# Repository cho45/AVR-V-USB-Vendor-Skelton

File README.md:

AVR V-USB custom class skelton project
======================================

AVR + V-USB でカスタムUSBデバイスを作るスケルトン
V-USB がスタンダードなリクエストには答えてくれるのでかなり簡潔に書ける。

このデバイスに接続するためのホスト実装のサンプル

 * [./sketch.rb]( ./sketch.rb ) libusb + ruby
 * [./sketch-chrome-app/]( ./sketch-chrome-app/ ) Chrome App

回路図の例 (Eagle)

 * [./circuit/]( ./circuit/ )

## 背景

Mac の場合 HID デバイスへの低レベルアクセスを OS が握っているため、
HID クラスとしてデバイスを作成すると、かえって面倒なことになる ( control_transfer は可能だが、claim_interface が不可能なので他のことは何もできない)。

## 覚書

 * USB_CFG_DEVICE_CLASS を 0xff (vendor)
 * USB_CFG_INTERFACE_CLASS を 0xff (vendor)

にしないとダメ (claim_interface が失敗)

ref.

 * http://vusb.wikidot.com/driver-api
 * http://vusb.wikidot.com/host-software

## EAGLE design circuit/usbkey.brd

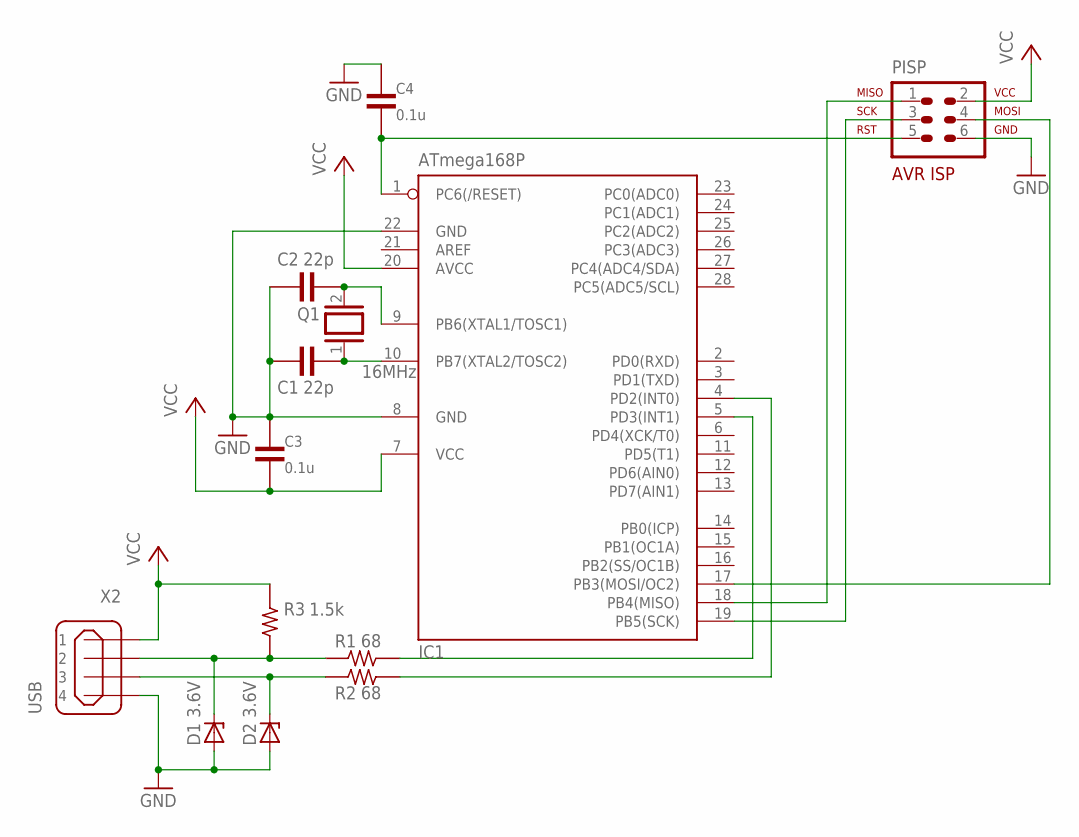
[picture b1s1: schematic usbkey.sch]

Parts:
C1, C2: 22p; 50-0302-2.54
C3, C4: 0.1u; 50-0302-2.54
D1, D2: 3.6V; DO35Z10
IC1: ATmega168P; DIL28-3
PISP: AVR-ISP-6VERT; AVR-ISP-6
Q1: 16MHz; QS
R1, R2: 68; 1/4W-7.62H
R3: 1.5k; 1/4W-2.54V
X2: USB; 85-32004-10X

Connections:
GND: C1.PAD2 (2), C2.PAD2 (2), C3.PAD1 (1), C4.PAD1 (1), D1.A, D2.A, IC1.8 (GND), IC1.22 (GND), PISP.6, X2.4
unnamed: C1.PAD1 (1), IC1.10 (PB7(XTAL2/TOSC2)), Q1.1
unnamed: C2.PAD1 (1), IC1.9 (PB6(XTAL1/TOSC1)), Q1.2
unnamed: IC1.5 (PD3(INT1)), R1.PAD2 (2)
unnamed: D2.C, R2.PAD1 (1), X2.3
unnamed: IC1.4 (PD2(INT0)), R2.PAD2 (2)
unnamed: D1.C, R1.PAD1 (1), R3.PAD1 (1), X2.2
unnamed: C4.PAD2 (2), IC1.1 (PC6(/RESET)), PISP.5
unnamed: IC1.17 (PB3(MOSI/OC2)), PISP.4
unnamed: IC1.19 (PB5(SCK)), PISP.3
unnamed: IC1.18 (PB4(MISO)), PISP.1
VCC: C3.PAD2 (2), IC1.7 (VCC), IC1.20 (AVCC), PISP.2, R3.PAD2 (2), X2.1

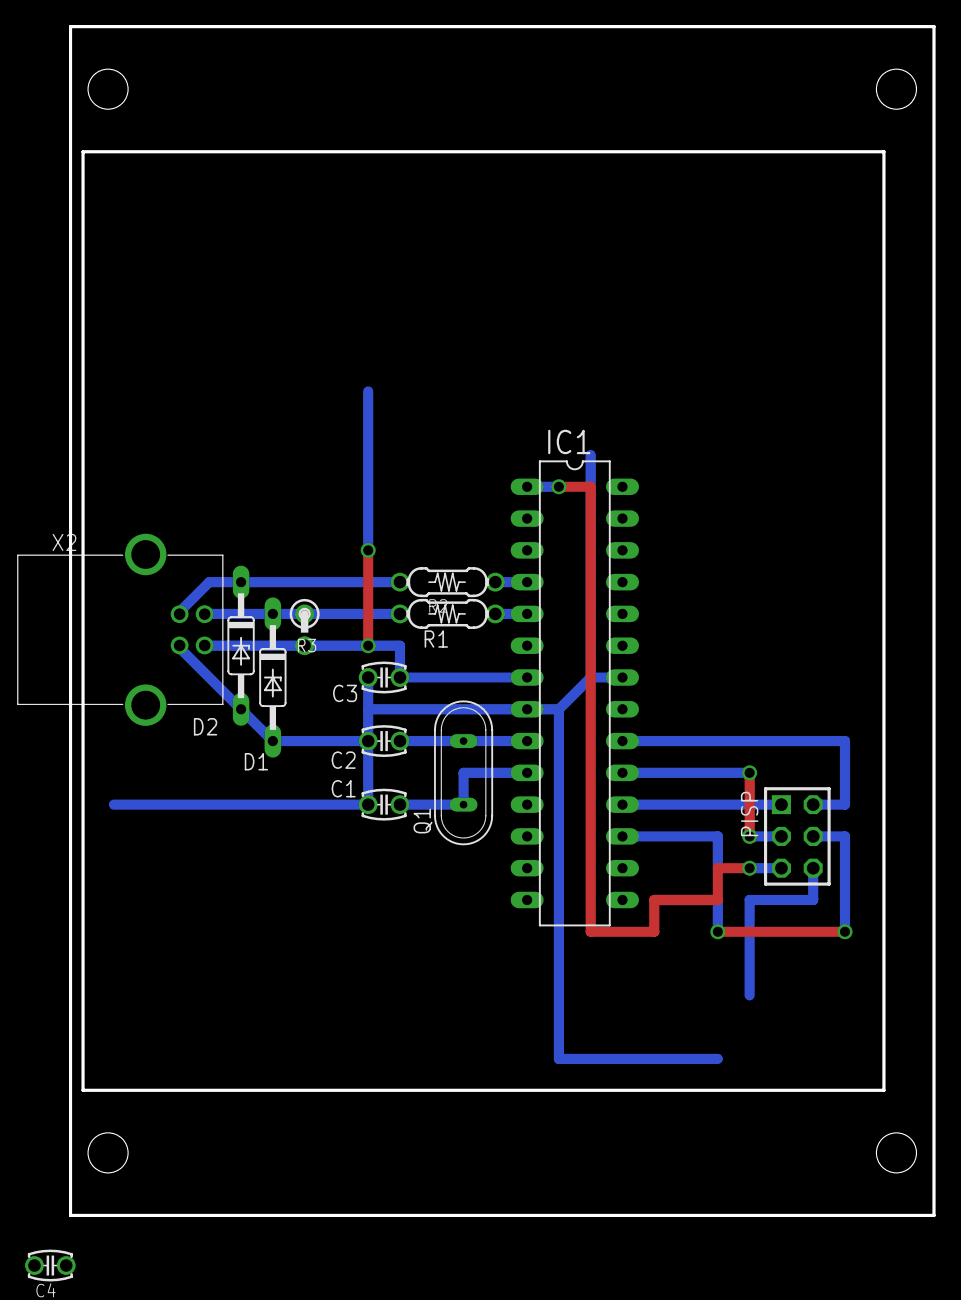
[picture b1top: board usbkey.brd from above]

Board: 2 copper layers, 69.0 x 95.0 mm, 13 parts (0 on the bottom side), 12 nets.

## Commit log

2014-07-11 init
